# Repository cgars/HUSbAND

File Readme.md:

--
HUSbAND -  High freqUency StimulAtioN Device
-------------

Is a Ardoino micro based stimulation eyglass. It is used for high precission stimulation with light flickering at different frequencies.
This repsoitory contains (or will contain)
* The firmware for the arduino 
* The schemata for the eypieces and the controll board
* PCB Designs for the eypieces and the controll board

--
 Usage
-------------
The device can be used by wrtiting a command strings to the serial port emulated by the arduinos ftdi usb chip. A command consists of a upper case letter (R,G,B,I,F,H,S,X,T) and sometimes a number (R,G,B,I,F,H,T) that is either 8 bit unsigned integer (R,G,B,I) or 32 bit unsigned integer (F,H,T). Due to the way the device uses counters the Frequency the device produces will not match the frequency set exactly but it tries to come as close as possible.

Command Letter | Values | Function
------------ | -------------|-------------
R|0-1023|Red leds
G|0-1023|Green leds
B|0-1023|Blue leds
F|0-15000HZ|Frequency1
H|0-15000Hz|Frequency2
T|0-99999|Time in ms between onset of freq1 and freq2
S||Start the Device
X||Stop the Device

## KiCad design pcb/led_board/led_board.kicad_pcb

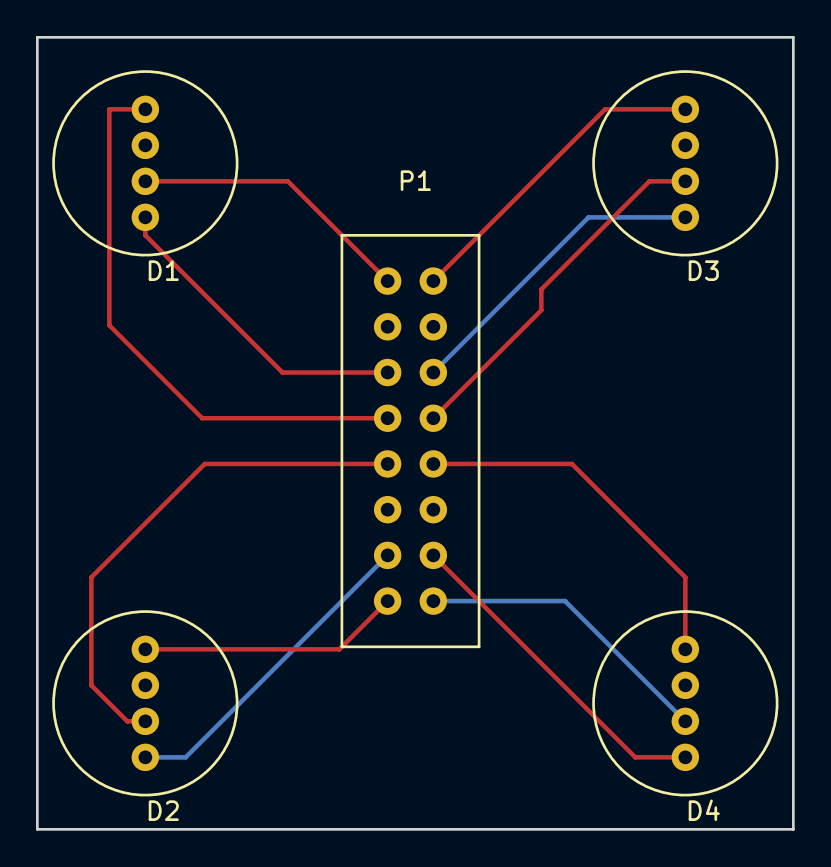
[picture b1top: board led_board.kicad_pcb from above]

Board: 2 copper layers, 42.0 x 44.0 mm, 5 parts (0 on the bottom side), 13 nets.

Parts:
D1, D2, D3, D4: LED_BCRG; RGB_LED_BCRG
P1: CONN_02X08; Buchsenleiste

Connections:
GND: D1.2, D2.2, D3.2, D4.2, P1.3, P1.4, P1.11, P1.12
unnamed: D1.1, P1.7
unnamed: D1.3, P1.1
unnamed: D1.4, P1.5
unnamed: D2.1, P1.15
unnamed: D2.3, P1.9
unnamed: D2.4, P1.13
unnamed: D3.1, P1.2
unnamed: D3.3, P1.8
unnamed: D3.4, P1.6
unnamed: D4.1, P1.10
unnamed: D4.3, P1.16
unnamed: D4.4, P1.14

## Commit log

2015-03-06 Fixed wrong delay timing
2015-03-06 printf no floats fix
2015-03-06 10 bit Counter now 8kHz
2015-03-10 writing directly into the 4D register (no analogwrite)
2015-03-10 write directly to the led trigger pin resisters
2015-03-10 back to digital write
2015-03-11 LED trigger write directly again
2015-03-11 Clear OC resisters before writing
2015-03-26 no PWM on the main on/off pin anymore
2015-03-27 Test frequency va counter 4
2015-03-27 1023 not 1023 damn it
2015-03-27 Clear PWM modes
2015-03-27 Set OCR4C as top for timer 4
2015-03-27 Added gui
2015-03-30 No more analog write for the 16 Bit registers
2015-03-30 GUI now 10bit for colors
2015-03-30 Fix: Set INTPIN to OUTPUT
2015-03-30 No serial write upon command
2015-03-30 Fix: green value is now read from input
2015-03-30 Fnd the best prescaler automatically
2015-03-30 Added more prescaler
2015-03-31 Fix: Correct counting (added -1)
2015-04-13 FIX: correct arduiono clock time (15mHz->16mHz)
2015-04-13 Fix: CLOCK double
2015-04-21 Fix: Disconnect TC1 on 0 setting
    otherwise it is still high for 1 clock cycle
2015-04-27 Switch to interuppt counting for Flicker generation
    To insure that led will only switch of after duty cycle end the flicker
    pin should only toggle when duty cycle is complete. this way it is
    ensured that stmuli will always have same intensity
2015-04-27 Switch on Timer1 interupts
2015-04-27 Fix: FREQCOUNTER-> Double
2015-04-27 UPGRADE: write directly tpo ports instead of digitalWrite
2015-04-27 Fix: Get correct outregs for freq and trigger pin and Gui 0-255
2015-04-28 Upgrade: intrerupt variable with max pwm channel
2015-05-04 Added experiment controll routine
2015-05-04 Fix: missing carriage return in experiment control
2015-05-04 Feature: Use formatted time for experiment files
2015-05-04 IMP: Document times abd frequencies ind the experiment File
2015-05-04 Imp: Test setup
2015-05-05 Fix: Only change stimulation Frequency when cycle complete
2015-05-05 FIX: Updated all ISR (not only one)
2015-05-05 IMP: Initialize colors as white
2016-01-05 Imp: Readme
2016-01-11 Imp: Added some more comments
2016-01-11 New: Added the mainboard pcb designs
2016-01-11 Imp: Readme updated
2016-01-11 Fix: Declaredwq FREQ
2016-01-11 Add: .travis.yml
2016-01-11 Imp: Added Travis Image to Readme
2016-01-12 New: Added the led eyepeace pcb designs
2016-02-22 Imp: Spelling
2016-03-22 Imp:
2016-03-22 Revert "Imp:"
    This reverts commit 673a2968348ef17a28b7ab124658b451d2fabc26.
2016-03-22 Imp: Reprogram Device to test the frequenbcy transition
2016-03-22 Imp: Updated Readme
2016-04-07 Imp: Time till frequency switch can be larger than 2s
2016-04-11 Imp: Switch frequency on F command. Only change to H frequency after S
2016-07-27 Imp: Introduced second Trigger
